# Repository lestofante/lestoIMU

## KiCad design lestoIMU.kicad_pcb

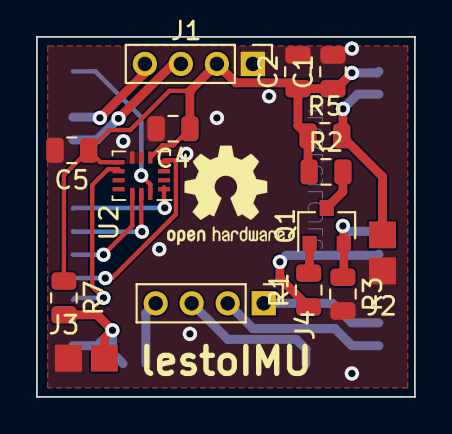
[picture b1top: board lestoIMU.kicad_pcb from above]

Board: 2 copper layers, 21.0 x 20.0 mm, 17 parts (1 on the bottom side), 20 nets.

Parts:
C1: 22uF; C_0805_2012Metric
C2: 100nF; C_0805_2012Metric
C4, C5: 100nf; C_0805_2012Metric
J1: PRG; PinHeader_1x04_P2.00mm_Vertical
J2: RST; PinHeader_smd_bridge_1x02_P2.00mm_SMD
J3: PRG; PinHeader_smd_bridge_1x02_P2.00mm_SMD
J4: JTAG; PinHeader_1x04_P2.00mm_Vertical
LOGO1: Logo_Open_Hardware_Small; OSHW-Logo2_7.3x6mm_SilkScreen
Q1: Q_NMOS_GSD; SOT-23
R1: 1K; R_0805_2012Metric
R2: 33K; R_0805_2012Metric
R3, R5, R7: 10K; R_0805_2012Metric
U1: ESP32-WROOM-32D; ESP32-WROOM-32
U2: BMI160; Bosch_LGA-14_3x2.5mm_P0.5mm

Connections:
+3V3: C1.1, C2.1, C4.1, C5.1, J1.2, R2.1, R5.1, R7.1, U1.2, U2.5, U2.8
ADC: Q1.2, R3.1, U1.9
BOOT: J3.2, R7.2, U1.24, U1.25
CLK: U1.30, U2.13
CS: U1.29, U2.12
ENABLE: J2.2, R5.2, U1.3
EN_ADC: R1.1, U1.10
GND: C1.2, C2.2, C4.2, C5.2, J1.1, J2.1, J3.1, R3.2, U1.1, U1.15, U1.38, U1.39, U2.6, U2.7
INT1: U1.28, U2.4
INT2: U1.27, U2.9
MISO: U1.31, U2.1
MOSI: U1.37, U2.14
MTCK: J4.3, U1.16
MTDI: J4.2, U1.14
MTDO: J4.4, U1.23
MTMS: J4.1, U1.13
unnamed: Q1.1, R1.2
unnamed: Q1.3, R2.2
RX: J1.3, U1.34
TX: J1.4, U1.35

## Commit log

2020-07-18 first upload
2020-07-18 added license
2020-10-06 major update
